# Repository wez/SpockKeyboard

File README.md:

# "Spock" Keyboard

This repo holds schematics and code for the Spock keyboard that was
designed by me (Wez Furlong) and modeled on my hands.

The keyboard is a split ergonomic layout in an ortholinear (straight columns,
aligned to your fingers rather than staggered) arrangement with splayed columns
that more closely match the finger separation when the hand is at rest,
thumb clusters to make use of the strong but underused thumbs and a cluster
for classic inverted-T arrow keys.

The Spock name comes from the finger splay which is reminiscent of the Vulcan
hand gesture.

The initial hardware revision is designed around a prototyping friendly
arrangement, with the PCB set up with a minimized keyboard matrix (saving the
headache of routing the matrix while soldering) that is terminated at header
blocks.  No controller hardware is proscribed, making this a more convenient
physical base for experimenting with different controller and interfaces (USB,
BLE and so on).

## What's in this repo?

The hardware directory holds the kicad pcb defintion, gerber files and plate
definitions suitable for building a sandwich style case.  The PCB and gerber
files meet the DRC requirements for [Seeed's PCB fabrication service](https://www.seeedstudio.com/fusion_pcb.html).
The case design files are suitable for use with [Ponoko's service](http://www.ponoko.com).

The Spockduino directory holds some basic code for a keyboard firmware that uses
the Adafruit Feather M0 Express controller, and a SparkFun SX1509 breakout to
implement a USB keyboard.

## Keyboard Layout Editor

You can view the layout for the left hand here:

http://www.keyboard-layout-editor.com/#/gists/912c57ebc2bcc78ba9ccc6bbb83db161

## Bill of Materials

Should you decide to build one of these for yourself, you will need:

* 84 x Cherry MX compatible PCB mount key switches (each half requires 42)
* 70 x 1u Cherry MX key caps
* 8 x 1.25u Cherry MX key caps
* 6 x 1.5u Cherry MX key caps
* 84 x 1N4148 signal diodes
* 20 x M3 spacer to hold the case top and bottom apart.  Choose the height
  that meets your taste and internal electroncs selection.
* 20 x M3 nuts
* 20 x M3 screws
* Top and bottom plate.  See [hardware/spock-case-ponoko-p2.svg](https://github.com/wez/SpockKeyboard/blob/master/hardware/spock-case-ponoko-p2.svg) for left+right and top+bottom.
  I recommend using matte acrylic for its appealing combination of weight, appearance and price.
  Note that you don't strictly need the plates if you want to rock a bare PCB, but you should
  take care to avoid shorting the contacts under the PCB.
* 2x 2x12 header block.  Pick this to match your wiring.  I used right angled
  male header block to save on vertical space.
* Microcontroller of your choice.  I'm using an [Adafruit Feather M0 Express](https://www.adafruit.com/product/3403)
  with the Spockduino code.  You should be able to use other Feather boards without
  changing the wiring.
* 1x [SX1509 IO Expander](https://www.sparkfun.com/products/13601)
* Misc jumper wires
* 2x Jack and 1x connecting cable with 4+ wires.  Some folks like [TRRS](https://www.sparkfun.com/products/11570) audio cables and
  jacks, and others like [RJ45 jacks](https://www.sparkfun.com/products/643) ([+breakout](https://www.sparkfun.com/products/716)) and cables.

note: you can trade two of the 1.25u key caps in the thumb clusters for 1u to make
room to trade two of the other 1.25u caps with 1.5u caps for a total of 72x 1u caps,
4x 1.25u caps and 8x 1.5u caps.

There are no explicitly designed in attachment points for the controller, expander
or jacks so you may want to apply friction, tape or hot glue as suits your taste
and overall assembly.

## Wiring/Assembly

The PCB is reversible and can be used for a left or right hand.  For left hand
assembly you will place the switches and diodes on the side that has the
keyswitch labels (eg: `k01` through `k77`).  For the right hand you will place
them on the other side of the board.

If you are using the top plate, take care to assemble in the order described
below as it can be difficult to go back to correct a missed step once you
start soldering the keyswitches.

This initial rev is designed for prototyping, so I attached header to the Feather
and expander breakout boards and used jumper cables to connect them up.  Play
around with this before you start soldering keyswitches to make sure that you
can fit everything together.

1. Solder the diodes first.  The black bar of the diode must be aligned to the thicker
   white bar.  For the left hand the diodes go in on the side with the `dkXX` labels,
   for the right hand they go on the opposite side. 
2. Solder the header block second.  If you are using a plate the header pins must be
   on the other side of the board from the diodes.  If you are rocking a plateless
   build then you may want the header pins on the top side. 
3. If using a plate, insert the M3 nuts and spacers now.  The nuts go on the same side
   as the diodes, with the spacers on the other side.
4. Place the plate; it goes on the same side as the diodes and should click in
   and lightly grip on the top of the M3 spacers where they protude through
   the M3 nuts
5. Place the key switches through the plate.  The switch stem should be on the same
   side of the board as the diodes and plate.  The switch should friction fit
   in the PCB.  Take care to check that both of the pins on the underside of
   the switch are protuding from the holds on the reverse of the PCB.  You should
   see the pins in the holes and they may protude by about 1mm.  It is possible to
   fold a pin over when placing it, so you may need to wiggle it out of the plate and pcb and
   straighten up the pin.   Make sure that you check every switch!
6. Satisfy yourself that you can assemble the case and house the controller and expander
   before you go further.
7. Solder in the key switches.  Make sure that you solder both pins on each switch!

The Spockduino code assumes that you connected the pins like this:

### Feather

The Feather is attached to the left hand.  Take care: the header block
labels on the backside are wrong; see the errata below!

* Pins labelled `A0`-`A5` on the left side are connected to `r0`-`r5` in the header block
* Pins labelled `5`-`12` on the right side are connected to `c0`-`c6` in the header block
* `3V3`, `GND`, `SDA`, `SDL` are connected to the pins with the same names
  on the IO expander.  These 4 lines are intended to be carried over
  the connecting cable between the halves so you may want to connect the
  feather to a TRRS or RJ45 block and do the same on the other half
  for the Expander

### SX 1509

The SX1509 is attached to the right hand. Take care: the header block
labels on the backside are wrong; see the errata below!

* Pins `0`-`5` are connected to `r0`-`r5` in the header block.
* Pins `8`-`14` are connected to `c0`-`c6` in the header block.
* `3V3`, `GND`, `SDA`, `SDL` are connected to the pins with the same names
  on the Feather as noted above.

### Flashing

Use the arduino IDE to upload the spock sketch to the device.  I found
that this often requires a couple of attempts with the Feather M0 Express,
as the bootloader seems to take a little longer to kick in than the uploader
expects.

## Errata

The first and current rev of the PCB design has incorrect labels for the header
block on the back side of the PCB.  The labels on the front side are correct.
In case you are unsure which is the front, the front side of the pcb also has
labels for the switch positions.

## License and Copying

Unless stated in individual files, the contents of this repo are made available
under the terms of the MIT License.

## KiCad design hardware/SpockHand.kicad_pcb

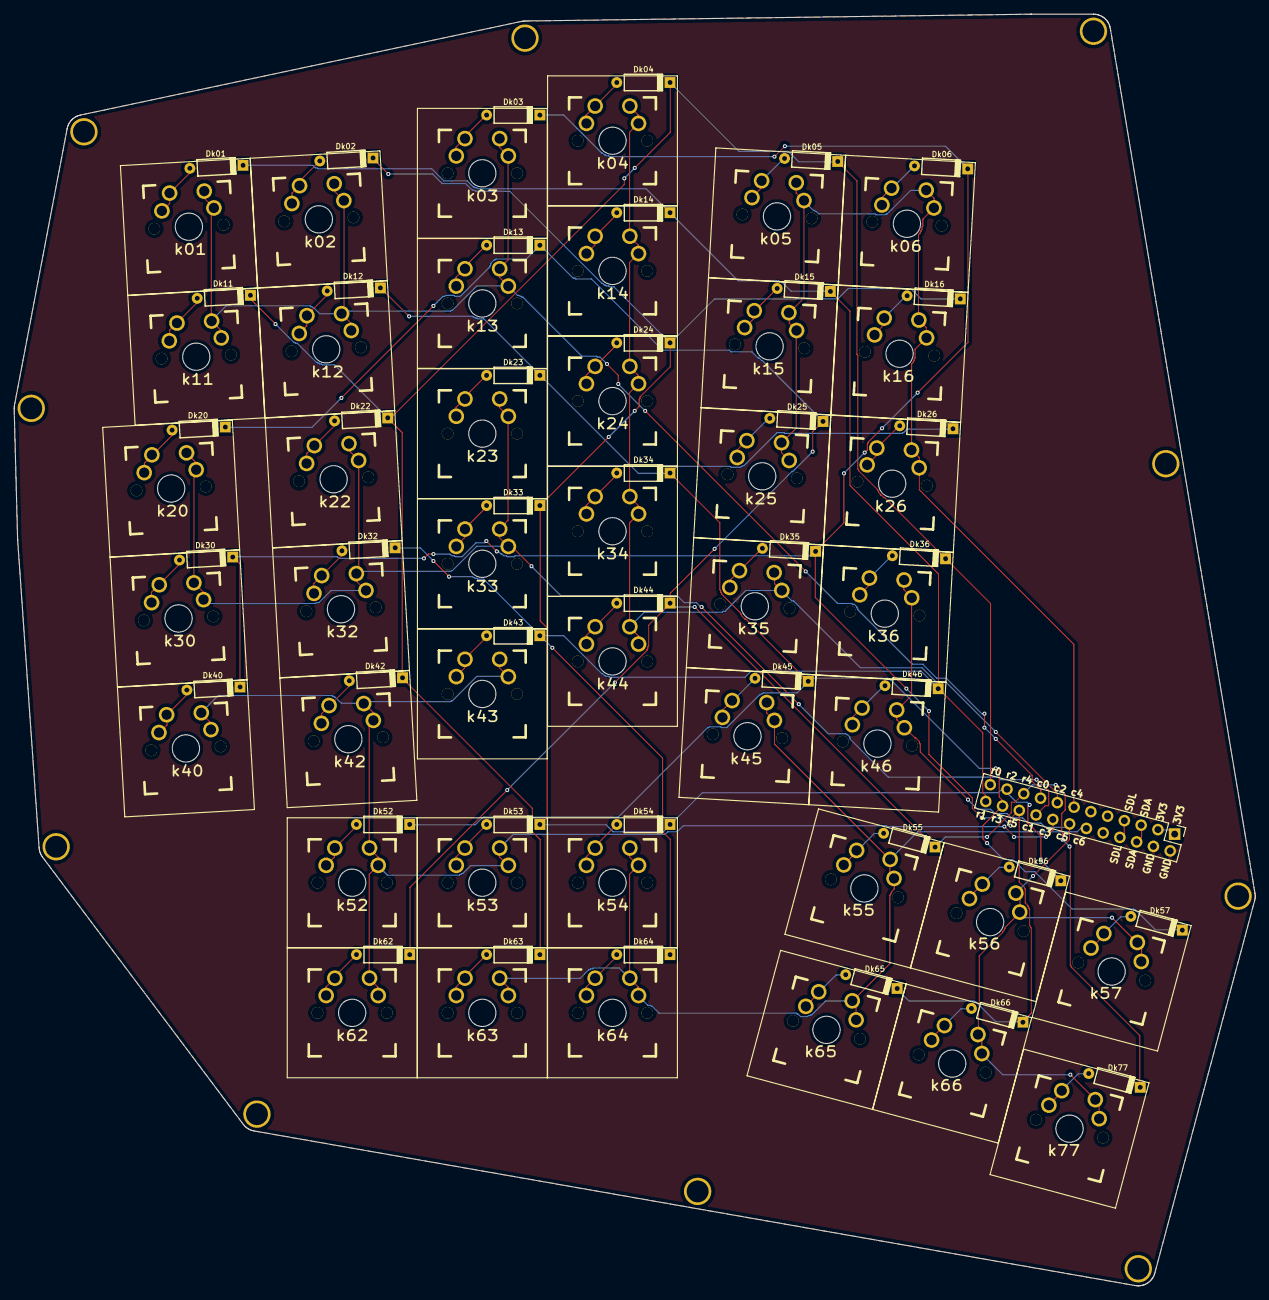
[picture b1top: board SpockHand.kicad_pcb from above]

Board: 2 copper layers, 181.6 x 186.1 mm, 94 parts (0 on the bottom side), 55 nets.

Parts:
CP0: VAL**; CP0
CP1: VAL**; CP1
CP2: VAL**; CP2
CP3: VAL**; CP3
CP4: VAL**; CP4
CP5: VAL**; CP5
CP6: VAL**; CP6
CP7: VAL**; CP7
CP8: VAL**; CP8
CP9: VAL**; CP9
Dk01: D; Dk01
Dk02: D; Dk02
Dk03: D; Dk03
Dk04: D; Dk04
Dk05: D; Dk05
Dk06: D; Dk06
Dk11: D; Dk11
Dk12: D; Dk12
Dk13: D; Dk13
Dk14: D; Dk14
Dk15: D; Dk15
Dk16: D; Dk16
Dk20: D; Dk20
Dk22: D; Dk22
Dk23: D; Dk23
Dk24: D; Dk24
Dk25: D; Dk25
Dk26: D; Dk26
Dk30: D; Dk30
Dk32: D; Dk32
Dk33: D; Dk33
Dk34: D; Dk34
Dk35: D; Dk35
Dk36: D; Dk36
Dk40: D; Dk40
Dk42: D; Dk42
Dk43: D; Dk43
Dk44: D; Dk44
Dk45: D; Dk45
Dk46: D; Dk46
Dk52: D; Dk52
Dk53: D; Dk53
Dk54: D; Dk54
Dk55: D; Dk55
Dk56: D; Dk56
Dk57: D; Dk57
Dk62: D; Dk62
Dk63: D; Dk63
Dk64: D; Dk64
Dk65: D; Dk65
Dk66: D; Dk66
Dk77: D; Dk77
k01: >VALUE; k01
k02: >VALUE; k02
k03: >VALUE; k03
k04: >VALUE; k04
k05: >VALUE; k05
k06: >VALUE; k06
k11: >VALUE; k11
k12: >VALUE; k12
k13: >VALUE; k13
k14: >VALUE; k14
k15: >VALUE; k15
k16: >VALUE; k16
k20: >VALUE; k20
k22: >VALUE; k22
k23: >VALUE; k23
k24: >VALUE; k24
k25: >VALUE; k25
k26: >VALUE; k26
k30: >VALUE; k30
k32: >VALUE; k32
k33: >VALUE; k33
k34: >VALUE; k34
k35: >VALUE; k35
k36: >VALUE; k36
k40: >VALUE; k40
k42: >VALUE; k42
k43: >VALUE; k43
k44: >VALUE; k44
k45: >VALUE; k45
k46: >VALUE; k46
k52: >VALUE; k52
k53: >VALUE; k53
k54: >VALUE; k54
k55: >VALUE; k55
k56: >VALUE; k56
k57: >VALUE; k57
k62: >VALUE; k62
k63: >VALUE; k63
k64: >VALUE; k64
k65: >VALUE; k65
k66: >VALUE; k66
k77: >VALUE; k77

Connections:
unnamed: Dk11.2, k11.2, k11.2a
unnamed: Dk22.2, k22.2, k22.2a
unnamed: Dk04.2, k04.2, k04.2a
unnamed: Dk42.2, k42.2, k42.2a
unnamed: Dk05.2, k05.2, k05.2a
unnamed: Dk36.2, k36.2, k36.2a
unnamed: Dk63.2, k63.2, k63.2a
unnamed: Dk01.2, k01.2, k01.2a
unnamed: Dk32.2, k32.2, k32.2a
unnamed: Dk14.2, k14.2, k14.2a
unnamed: Dk43.2, k43.2, k43.2a
unnamed: Dk15.2, k15.2, k15.2a
unnamed: Dk46.2, k46.2, k46.2a
unnamed: Dk64.2, k64.2, k64.2a
unnamed: Dk02.2, k02.2, k02.2a
unnamed: Dk33.2, k33.2, k33.2a
unnamed: Dk24.2, k24.2, k24.2a
unnamed: Dk53.2, k53.2, k53.2a
unnamed: Dk16.2, k16.2, k16.2a
unnamed: Dk56.2, k56.2, k56.2a
unnamed: Dk54.2, k54.2, k54.2a
unnamed: Dk12.2, k12.2, k12.2a
unnamed: Dk23.2, k23.2, k23.2a
unnamed: Dk34.2, k34.2, k34.2a
unnamed: Dk52.2, k52.2, k52.2a
unnamed: Dk26.2, k26.2, k26.2a
unnamed: Dk57.2, k57.2, k57.2a
unnamed: Dk45.2, k45.2, k45.2a
unnamed: Dk13.2, k13.2, k13.2a
unnamed: Dk20.2, k20.2, k20.2a
unnamed: Dk44.2, k44.2, k44.2a
unnamed: Dk62.2, k62.2, k62.2a
unnamed: Dk25.2, k25.2, k25.2a
unnamed: Dk77.2, k77.2, k77.2a
unnamed: Dk55.2, k55.2, k55.2a
unnamed: Dk03.2, k03.2, k03.2a
unnamed: Dk30.2, k30.2, k30.2a
unnamed: Dk35.2, k35.2, k35.2a
unnamed: Dk40.2, k40.2, k40.2a
unnamed: Dk06.2, k06.2, k06.2a
unnamed: Dk66.2, k66.2, k66.2a
unnamed: Dk65.2, k65.2, k65.2a
col0: k01.1, k01.1a, k02.1, k02.1a, k03.1, k03.1a, k11.1, k11.1a, k12.1, k12.1a, k13.1, k13.1a
col1: k20.1, k20.1a, k22.1, k22.1a, k23.1, k23.1a, k30.1, k30.1a, k32.1, k32.1a, k33.1, k33.1a
col2: k04.1, k04.1a, k14.1, k14.1a, k24.1, k24.1a, k34.1, k34.1a, k35.1, k35.1a, k44.1, k44.1a
col3: k40.1, k40.1a, k42.1, k42.1a, k43.1, k43.1a, k52.1, k52.1a, k53.1, k53.1a, k62.1, k62.1a
col4: k05.1, k05.1a, k06.1, k06.1a, k15.1, k15.1a, k16.1, k16.1a, k25.1, k25.1a, k26.1, k26.1a
col5: k36.1, k36.1a, k46.1, k46.1a, k56.1, k56.1a, k57.1, k57.1a, k66.1, k66.1a, k77.1, k77.1a
col6: k45.1, k45.1a, k54.1, k54.1a, k55.1, k55.1a, k63.1, k63.1a, k64.1, k64.1a, k65.1, k65.1a
row0: Dk04.1, Dk05.1, Dk11.1, Dk22.1, Dk36.1, Dk42.1, Dk63.1
row1: Dk01.1, Dk14.1, Dk15.1, Dk32.1, Dk43.1, Dk46.1, Dk64.1
row2: Dk02.1, Dk16.1, Dk24.1, Dk33.1, Dk53.1, Dk54.1, Dk56.1
row3: Dk12.1, Dk23.1, Dk26.1, Dk34.1, Dk45.1, Dk52.1, Dk57.1
row4: Dk13.1, Dk20.1, Dk25.1, Dk44.1, Dk55.1, Dk62.1, Dk77.1
row5: Dk03.1, Dk06.1, Dk30.1, Dk35.1, Dk40.1, Dk65.1, Dk66.1

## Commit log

2018-04-08 Add spock keyboard bits
2018-04-08 Add some images
2018-04-08 add links to some of the components
2018-04-08 tweak the readme a bit more
2018-04-12 add some extended keys
2018-04-12 fix keyboard usb descriptor so that extended keys work
2018-04-12 fix dual role ctrl/esc tap and hold behavior
2018-04-12 Use a more targeted sx1509 driver
    The example sparkfun driver does a ton of IO for every operation,
    which eats into our headroom for responding to keypresses.
2018-07-17 bitrot
